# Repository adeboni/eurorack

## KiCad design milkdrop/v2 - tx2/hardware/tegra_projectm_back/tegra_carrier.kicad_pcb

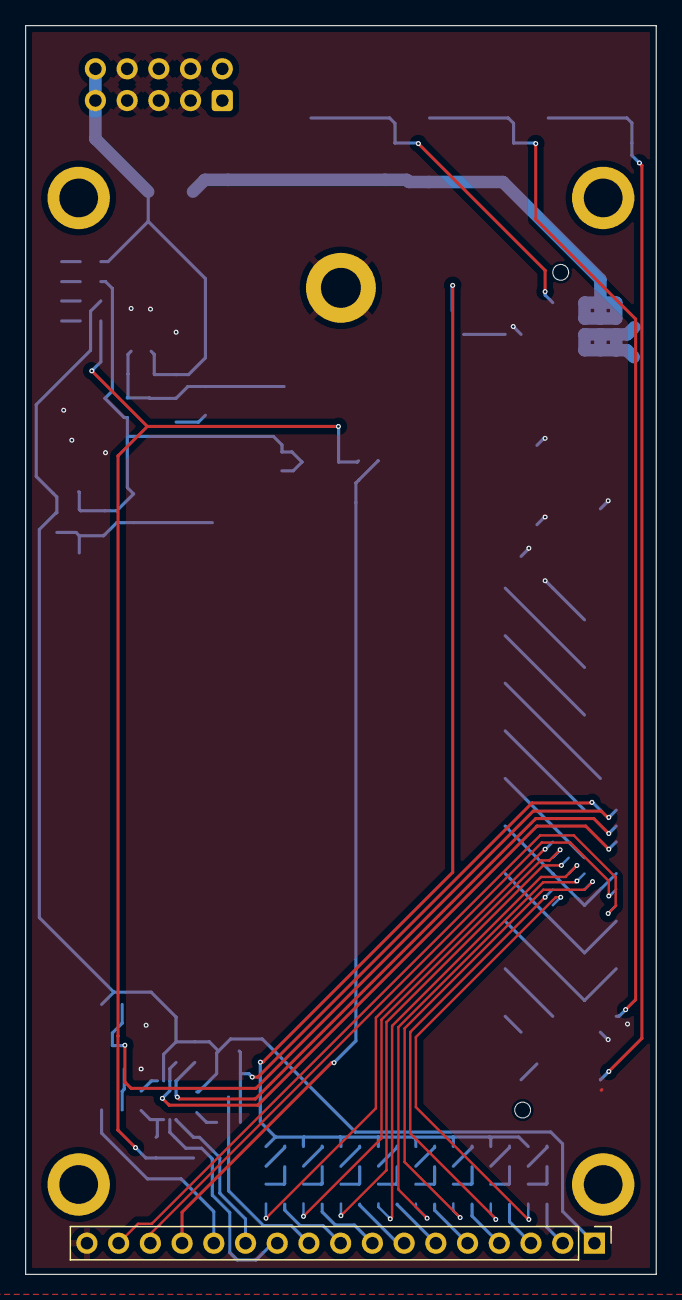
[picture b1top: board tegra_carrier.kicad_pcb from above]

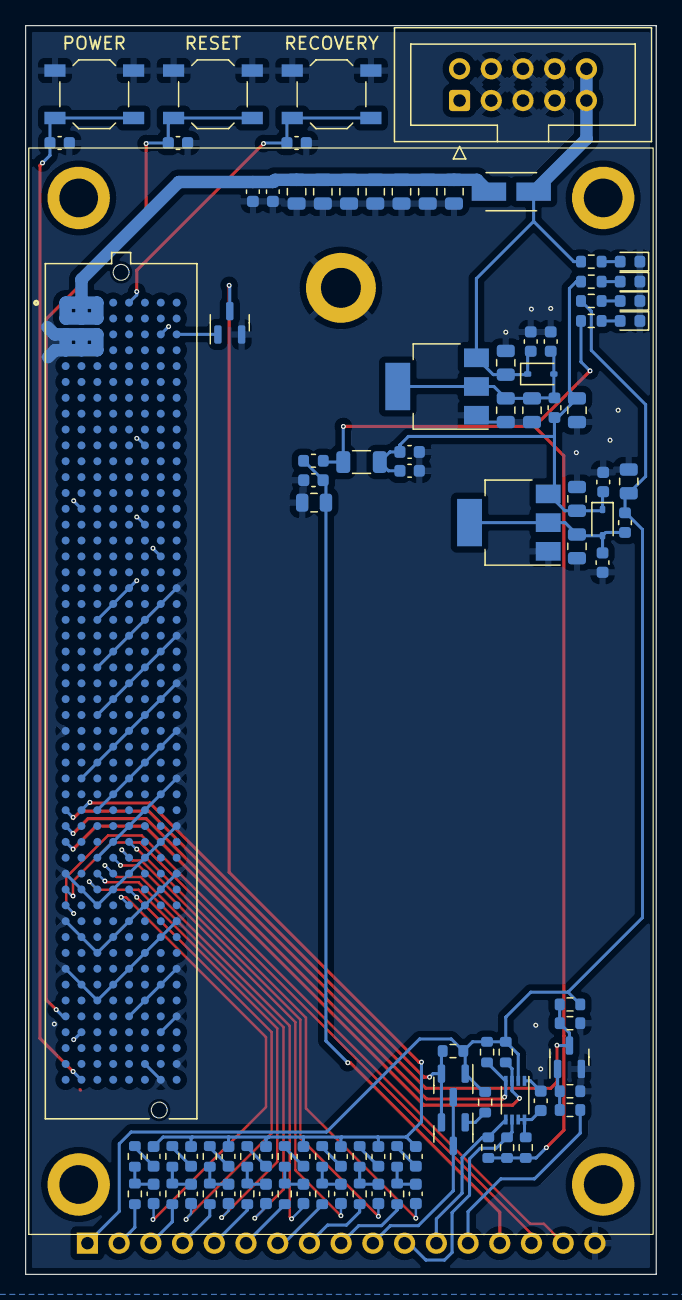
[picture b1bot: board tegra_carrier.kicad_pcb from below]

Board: 2 copper layers, 50.5 x 100.0 mm, 100 parts (99 on the bottom side), 63 nets.

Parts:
C1, C2, C3, C4, C5, C6, C7, C8, C9, C10, C17, C26, C38: 22u; C_0805_2012Metric
C11, C12, C13, C18, C20, C24, C25, C28, C29, C30, C31, C32, C33, C34, C35, C44: 100n; C_0603_1608Metric
C14, C15, C27: 10n; C_0603_1608Metric
C16, C19: 47u; C_0805_2012Metric
C22: 100p; C_0603_1608Metric
C23: 10u; C_0603_1608Metric
D1, D2: 1N5819WS; D_SOD-323
D3, D6, D26, D28: LED; LED_0603_1608Metric
D4: BAS70-05-7-F; SOT-23
FB1, FB2: MPZ1608S221; L_0603_1608Metric
H1: MountingHole_Pad; MountingHole_3.2mm_M3_DIN965_Pad
J1: SEAM-50-02.0-S-08-2-A-K-TR; SAMTEC_SEAM-50-02.0-S-08-2-A-K-TR
J3: Conn_02x05_Odd_Even; IDC-Header_2x05_P2.54mm_Vertical
J4: Conn_01x17; PinHeader_1x17_P2.54mm_Vertical
L1: BLM18AG102; L_0603_1608Metric
L2, L3, L4, L5, L6, L7, L8, L9: MI0603J601R-10; L_0603_1608Metric
L11: FERRITE_10A; FB_28F0121-0SR-10
Q1: BC846; SOT-23
Q2, Q5: BSS138; SOT-23
R1: 330; R_0603_1608Metric
R4, R6: 10k; R_0603_1608Metric
R7, R9: 100k; R_0603_1608Metric
R10: 200k; R_0603_1608Metric
R11: 162k; R_0603_1608Metric
R13, R14, R15, R16, R55: 2.2k; R_0603_1608Metric
R18: 31.6k; R_0603_1608Metric
R22, R57: 1k; R_0603_1608Metric
R23, R24, R25, R26, R27, R28, R29, R30: 4.7; R_0603_1608Metric
R31, R32, R33, R34, R35, R36, R37, R38: 499; R_0603_1608Metric
SW1, SW2, SW3: SW_Push; SW_SPST_TL3342
TH1: 1206L020C; R_1206_3216Metric
U1: AMS1117-3.3; SOT-223-3_TabPin2
U3: PCA9306DC; VSSOP-8_2.3x2mm_P0.5mm
U15: AMS1117-5.0; SOT-223-3_TabPin2

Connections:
5V_HDMI: L1.1, R10.1, R15.1, R16.1, R22.1, TH1.1
+3V3: C16.1, FB2.2, J4.1, Q2.1 (G), R1.1, R4.1, R11.2, R13.1, R14.1, R18.2, U3.2 (VREF1)
+5V: C10.2, C17.1, C18.1, C23.1, C24.1, D2.1 (K), FB1.2, R57.1, TH1.2, U1.3 (VI)
+12V: C9.2, C44.1, D1.1 (K), J3.9, J3.10, L11.1, R55.1, U15.3 (VI)
DP1_TXD0_N: C29.1, J1.E38
DP1_TXD0_P: C28.1, J1.E39
DP1_TXD1_N: C31.1, J1.C37
DP1_TXD1_P: C30.1, J1.C38
DP1_TXD2_N: C33.1, J1.D36
DP1_TXD2_P: C32.1, J1.D37
DP1_TXD3_N: C35.1, J1.E35
DP1_TXD3_P: C34.1, J1.E36
FORCE_RECOVERY_L: C27.1, J1.E1, SW3.2
GND: C1.1, C2.1, C3.1, C4.1, C5.1, C6.1, C7.1, C8.1, C9.1, C10.1, C11.2, C12.2, C13.2, C14.2, C15.2, C16.2, C17.2, C18.2, C19.2, C20.2, C22.2, C23.2, C24.2, C25.2, C26.1, C27.2, C38.1, C44.2, D3.1 (K), D6.1 (K), D26.1 (K), D28.1 (K), H1.1, J1.A3, J1.A4, J1.A28, J1.A37, J1.A40, J1.A43, J1.B3, J1.B4, J1.B14, J1.B31, J1.B38, J1.B41, J1.B44, J1.B47, J1.C3, J1.C4, J1.C21, J1.C24, J1.C27, J1.C30, J1.C33, J1.C36, J1.C39, J1.C42, J1.C45, J1.D20, J1.D23, J1.D26, J1.D29, J1.D32, J1.D35, J1.D38, J1.D41, J1.D44, J1.E19, J1.E22, J1.E25, J1.E28, J1.E31, J1.E34, J1.E37, J1.E40, J1.E43, J1.E46, J1.F10, J1.F15, J1.F21, J1.F24, J1.F27, J1.F30, J1.F33, J1.F36, J1.F39, J1.F42, J1.F45, J1.F49, J1.G3, J1.G17, J1.G20, J1.G23, J1.G26, J1.G29, J1.G32, J1.G35, J1.G38, J1.G41, J1.G44, J1.G47, J1.G50, J1.H19, J1.H22, J1.H25, J1.H28, J1.H31, J1.H34, J1.H37, J1.H40, J1.H43, J1.H46, J1.H49, J3.3, J3.4, J3.5, J3.6, J3.7, J3.8, J4.17, Q1.2 (E), Q5.2 (S), R6.2, R9.2, SW1.1, SW2.1, SW3.1, U1.1 (GND), U3.1 (GND), U15.1 (GND)
HDMI_5V_CABLE: C25.1, C26.2, J4.14, L1.2
HDMI_CEC: D4.2 (A), J1.B33, Q2.2 (S), R11.1
HDMI_CEC_CON: D4.3 (K), J4.10, Q2.3 (D)
HDMI_CKN_CON: J4.9, R30.2
HDMI_CKP_CON: J4.8, R29.2
HDMI_D0N_CON: J4.7, R28.2
HDMI_D0P_CON: J4.6, R27.2
HDMI_D1N_CON: J4.5, R26.2
HDMI_D1P_CON: J4.4, R25.2
HDMI_D2N_CON: J4.3, R24.2
HDMI_D2P_CON: J4.2, R23.2
HDMI_DDC_SCL_5V0: J4.11, R15.2, U3.6 (SCL2)
HDMI_DDC_SCL_POL: J1.A35, R13.2, U3.3 (SCL1)
HDMI_DDC_SDA_5V0: J4.12, R16.2, U3.5 (SDA2)
HDMI_DDC_SDA_POL: J1.A34, R14.2, U3.4 (SDA1)
HDMI_HPD_CON: J4.13, R7.2
HDMI_HPD_L: J1.A33, Q1.3 (C), R4.2, R6.1
unnamed: C28.2, R23.1, R31.2
unnamed: C29.2, R24.1, R32.2
unnamed: C30.2, R25.1, R33.2
unnamed: C31.2, R26.1, R34.2
unnamed: C32.2, R27.1, R35.2
unnamed: C33.2, R28.1, R36.2
unnamed: C34.2, R29.1, R37.2
unnamed: C35.2, R30.1, R38.2
unnamed: C7.2, C8.2, C13.1, D1.2 (A), FB1.1, U15.2 (VO)
unnamed: C19.1, C20.1, D2.2 (A), FB2.1, U1.2 (VO)
unnamed: D3.2 (A), R1.2
unnamed: D4.1 (A), R18.1
unnamed: D6.2 (A), R22.2
unnamed: D26.2 (A), R57.2
unnamed: D28.2 (A), R55.2
unnamed: L2.2, R31.1
unnamed: L3.2, R32.1
unnamed: L4.2, R33.1
unnamed: L5.2, R34.1
unnamed: L6.2, R35.1
unnamed: L7.2, R36.1
unnamed: L8.2, R37.1
unnamed: L9.2, R38.1
unnamed: Q1.1 (B), R7.1, R9.1
unnamed: L2.1, L3.1, L4.1, L5.1, L6.1, L7.1, L8.1, L9.1, Q5.3 (D)
unnamed: C22.1, R10.2, U3.7 (VREF2), U3.8 (EN)
P12V_TX2: C1.2, C2.2, C3.2, C4.2, C5.2, C6.2, C11.1, C12.1, C38.2, J1.A1, J1.A2, J1.B1, J1.B2, J1.C1, J1.C2, L11.2
POWER_BTN_L: C15.1, J1.B50, SW1.2
SOM_GPIO20_HDMI_TERM: J1.H3, Q5.1 (G)
SOM_RESET_OUT_L: C14.1, J1.A46, SW2.2
USB1_D_N: J1.A39, J4.16
USB1_D_P: J1.A38, J4.15

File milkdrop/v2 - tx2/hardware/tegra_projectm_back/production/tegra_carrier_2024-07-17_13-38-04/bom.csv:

Designator,Footprint,Quantity,Value,LCSC Part #
"C1, C10, C17, C2, C26, C3, C38, C4, C5, C6, C7, C8, C9",805,13,22u,C45783
"C11, C12, C13, C18, C20, C24, C25, C28, C29, C30, C31, C32, C33, C34, C35, C44",603,16,100n,C14663
"C14, C15, C27",603,3,10n,C57112
"C16, C19",805,2,47u,C16780
C22,603,1,100p,C14858
C23,603,1,10u,C96446
"D1, D2",D_SOD-323,2,1N5819WS,C191023
"D26, D28, D3, D6",603,4,LED,C2286
D4,SOT-23,1,BAS70-05-7-F,C134376
J1,SAMTEC_SEAM-50-02.0-S-08-2-A-K-TR,1,SEAM-50-02.0-S-08-2-A-K-TR,C6473445
L11,FB_28F0121-0SR-10,1,FERRITE_10A,C6341404
"FB1, FB2, L1, L2, L3, L4, L5, L6, L7, L8, L9",603,11,MI0603J601R-10,C1002
Q1,SOT-23,1,BC846,C20069134
"Q2, Q5",SOT-23,2,BSS138,C7420339
R1,603,1,330,C23138
R10,603,1,200k,C25811
R11,603,1,162k,C22813
"R13, R14, R15, R16, R55",603,5,2.2k,C4190
R18,603,1,31.6k,C4216
"R22, R57",603,2,1k,C21190
"R23, R24, R25, R26, R27, R28, R29, R30",603,8,4.7,C23164
"R31, R32, R33, R34, R35, R36, R37, R38",603,8,499,C23065
"R4, R6",603,2,10k,C25804
"R7, R9",603,2,100k,C25803
"SW1, SW2, SW3",SW_SPST_TL3342,3,SW_Push,C318884
TH1,1206,1,1206L020C,C207035
U1,SOT-223-3_TabPin2,1,AMS1117-3.3,C6186
U15,SOT-223-3_TabPin2,1,AMS1117-5.0,C6187
U3,VSSOP-8_2.3x2mm_P0.5mm,1,PCA9306DC,C33196

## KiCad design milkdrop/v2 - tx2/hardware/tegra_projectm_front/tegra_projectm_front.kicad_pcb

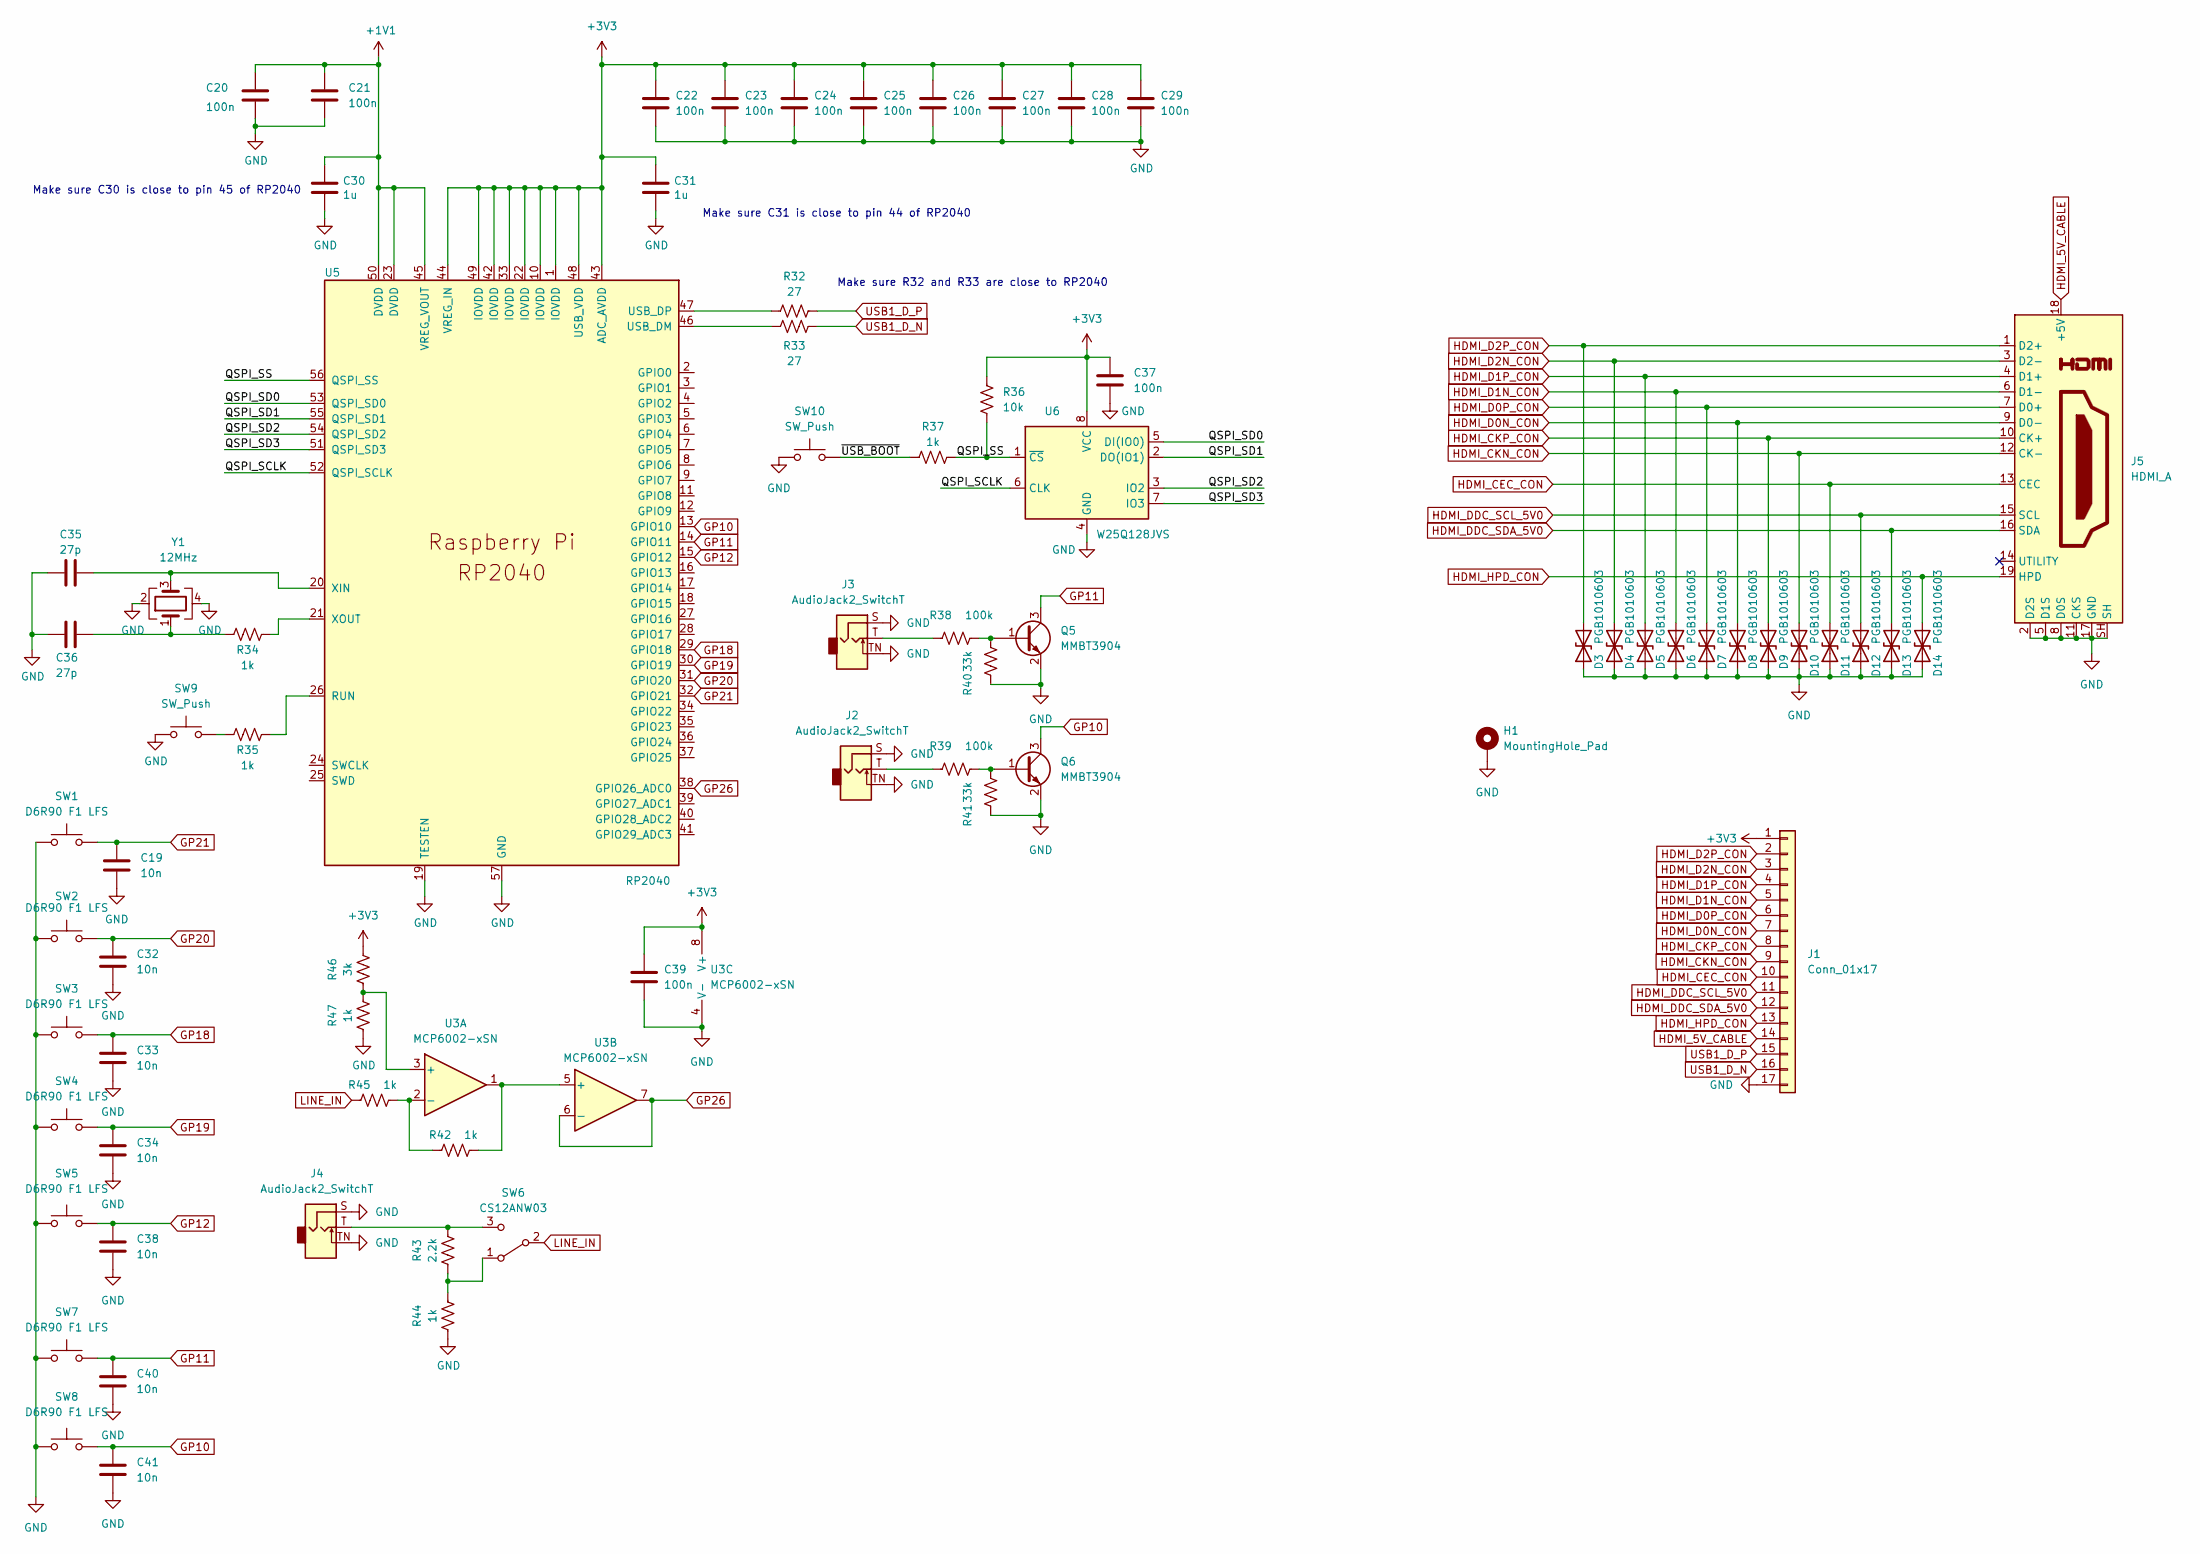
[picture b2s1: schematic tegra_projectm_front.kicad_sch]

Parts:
C19, C32, C33, C34, C38, C40, C41: 10n; C_0603_1608Metric
C20, C21, C22, C23, C24, C25, C26, C27, C28, C29, C37, C39: 100n; C_0603_1608Metric
C30, C31: 1u; C_0603_1608Metric
C35, C36: 27p; C_0603_1608Metric
D3, D4, D5, D6, D7, D8, D9, D10, D11, D12, D13, D14: PGB1010603; D_0603_1608Metric
H1: MountingHole_Pad; MountingHole_3.2mm_M3_DIN965_Pad
J1: Conn_01x17; PinSocket_1x17_P2.54mm_Vertical
J2, J3, J4: AudioJack2_SwitchT; Jack_3.5mm_QingPu_WQP-PJ398SM_Vertical_CircularHoles
J5: HDMI_A; MOLEX_476591101
Q5, Q6: MMBT3904; SOT-23
R32, R33: 27; R_0603_1608Metric
R34, R35, R37, R42, R44, R45, R47: 1k; R_0603_1608Metric
R36: 10k; R_0603_1608Metric
R38, R39: 100k; R_0603_1608Metric
R40, R41: 33k; R_0603_1608Metric
R43: 2.2k; R_0603_1608Metric
R46: 3k; R_0603_1608Metric
SW1, SW2, SW3, SW4, SW5, SW7, SW8: D6R90 F1 LFS; Push_E-Switch_KS01Q01
SW6: CS12ANW03
SW9, SW10: SW_Push; SW_SPST_TL3342
U3: MCP6002-xSN; SOIC-8_3.9x4.9mm_P1.27mm
U5: RP2040; QFN-56-1EP_7x7mm_P0.4mm_EP3.2x3.2mm
U6: W25Q128JVS; SOIC-8_5.23x5.23mm_P1.27mm
Y1: 12MHz; Crystal_SMD_3225-4Pin_3.2x2.5mm

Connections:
+1V1: C20.1, C21.1, C30.1, U5.23 (DVDD), U5.45 (VREG_VOUT), U5.50 (DVDD)
+3V3: C22.1, C23.1, C24.1, C25.1, C26.1, C27.1, C28.1, C29.1, C31.1, C37.1, C39.1, J1.1, R36.2, R46.1, U3.8 (V+), U5.1 (IOVDD), U5.10 (IOVDD), U5.22 (IOVDD), U5.33 (IOVDD), U5.42 (IOVDD), U5.43 (ADC_AVDD), U5.44 (VREG_IN), U5.48 (USB_VDD), U5.49 (IOVDD), U6.8 (VCC)
/QSPI_SCLK: U5.52 (QSPI_SCLK), U6.6 (CLK)
/QSPI_SD0: U5.53 (QSPI_SD0), U6.5 (DI(IO0))
/QSPI_SD1: U5.55 (QSPI_SD1), U6.2 (DO(IO1))
/QSPI_SD2: U5.54 (QSPI_SD2), U6.3 (IO2)
/QSPI_SD3: U5.51 (QSPI_SD3), U6.7 (IO3)
/QSPI_SS: R36.1, R37.2, U5.56 (QSPI_SS), U6.1 (~CS)
/~USB_BOOT: R37.1, SW10.2
GND: C19.2, C20.2, C21.2, C22.2, C23.2, C24.2, C25.2, C26.2, C27.2, C28.2, C29.2, C30.2, C31.2, C32.2, C33.2, C34.2, C35.2, C36.2, C37.2, C38.2, C39.2, C40.2, C41.2, D3.1 (A1), D4.1 (A1), D5.1 (A1), D6.1 (A1), D7.1 (A1), D8.1 (A1), D9.1 (A1), D10.1 (A1), D11.1 (A1), D12.1 (A1), D13.1 (A1), D14.1 (A1), H1.1, J1.17, J2.S, J2.TN, J3.S, J3.TN, J4.S, J4.TN, J5.2 (D2S), J5.5 (D1S), J5.8 (D0S), J5.11 (CKS), J5.17 (GND), J5.SH, Q5.2 (E), Q6.2 (E), R40.1, R41.1, R44.2, R47.2, SW1.1, SW2.1, SW3.1, SW4.1, SW5.1, SW7.1, SW8.1, SW9.1, SW10.1, U3.4 (V-), U5.19 (TESTEN), U5.57 (GND), U6.4 (GND), Y1.2, Y1.4
GP10: C41.1, Q6.3 (C), SW8.2, U5.13 (GPIO10)
GP11: C40.1, Q5.3 (C), SW7.2, U5.14 (GPIO11)
GP12: C38.1, SW5.2, U5.15 (GPIO12)
GP18: C33.1, SW3.2, U5.29 (GPIO18)
GP19: C34.1, SW4.2, U5.30 (GPIO19)
GP20: C32.1, SW2.2, U5.31 (GPIO20)
GP21: C19.1, SW1.2, U5.32 (GPIO21)
GP26: U3.6 (-), U3.7, U5.38 (GPIO26_ADC0)
HDMI_5V_CABLE: J1.14, J5.18 (+5V)
HDMI_CEC_CON: D11.2 (A2), J1.10, J5.13 (CEC)
HDMI_CKN_CON: D10.2 (A2), J1.9, J5.12 (CK-)
HDMI_CKP_CON: D9.2 (A2), J1.8, J5.10 (CK+)
HDMI_D0N_CON: D8.2 (A2), J1.7, J5.9 (D0-)
HDMI_D0P_CON: D7.2 (A2), J1.6, J5.7 (D0+)
HDMI_D1N_CON: D6.2 (A2), J1.5, J5.6 (D1-)
HDMI_D1P_CON: D5.2 (A2), J1.4, J5.4 (D1+)
HDMI_D2N_CON: D4.2 (A2), J1.3, J5.3 (D2-)
HDMI_D2P_CON: D3.2 (A2), J1.2, J5.1 (D2+)
HDMI_DDC_SCL_5V0: D12.2 (A2), J1.11, J5.15 (SCL)
HDMI_DDC_SDA_5V0: D13.2 (A2), J1.12, J5.16 (SDA)
HDMI_HPD_CON: D14.2 (A2), J1.13, J5.19 (HPD)
LINE_IN: R45.1, SW6.2 (B)
unnamed: C36.1, R34.2, Y1.1
unnamed: J2.T, R39.1
unnamed: J3.T, R38.1
unnamed: Q5.1 (B), R38.2, R40.2
unnamed: Q6.1 (B), R39.2, R41.2
unnamed: R35.2, SW9.2
unnamed: R43.2, R44.1, SW6.1 (A)
unnamed: J4.T, R43.1, SW6.3 (C)
unnamed: R46.2, R47.1, U3.3 (+)
unnamed: R42.1, R45.2, U3.2 (-)
unnamed: R42.2, U3.1, U3.5 (+)
unnamed: R35.1, U5.26 (RUN)
unnamed: R33.1, U5.46 (USB_DM)
unnamed: R32.1, U5.47 (USB_DP)
unnamed: C35.1, U5.20 (XIN), Y1.3
unnamed: R34.1, U5.21 (XOUT)
USB1_D_N: J1.16, R33.2
USB1_D_P: J1.15, R32.2

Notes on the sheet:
Make sure R32 and R33 are close to RP2040
Make sure C30 is close to pin 45 of RP2040
Make sure C31 is close to pin 44 of RP2040

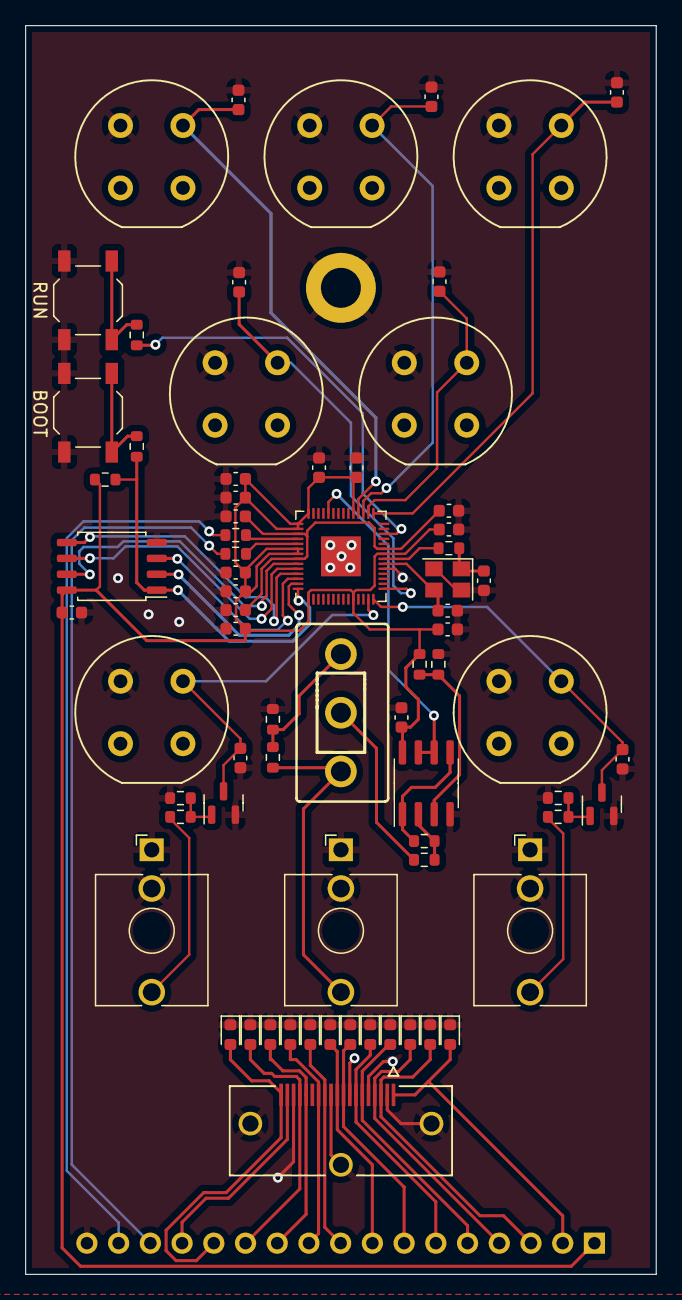
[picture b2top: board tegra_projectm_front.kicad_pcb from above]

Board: 2 copper layers, 50.5 x 100.0 mm, 73 parts (1 on the bottom side), 50 nets.

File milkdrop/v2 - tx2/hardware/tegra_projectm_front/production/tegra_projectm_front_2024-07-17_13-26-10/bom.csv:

Designator,Footprint,Quantity,Value,LCSC Part #
"C19, C32, C33, C34, C38, C40, C41",603,7,10n,C57112
"C20, C21, C22, C23, C24, C25, C26, C27, C28, C29, C37, C39",603,12,100n,C14663
"C30, C31",603,2,1u,C15849
"C35, C36",603,2,27p,C1647
"D10, D11, D12, D13, D14, D3, D4, D5, D6, D7, D8, D9",603,12,PGB1010603,C10677
J5,MOLEX_476591101,1,HDMI_A,C2682172
"Q5, Q6",SOT-23,2,MMBT3904,C20526
"R32, R33",603,2,27,C25190
"R34, R35, R37, R42, R44, R45, R47",603,7,1k,C21190
R36,603,1,10k,C25804
"R38, R39",603,2,100k,C25803
"R40, R41",603,2,33k,C4216
R43,603,1,2.2k,C4190
R46,603,1,3k,C4211
"SW10, SW9",SW_SPST_TL3342,2,SW_Push,C318884
U3,SOIC-8_3.9x4.9mm_P1.27mm,1,MCP6002-xSN,C7377
U5,QFN-56-1EP_7x7mm_P0.4mm_EP3.2x3.2mm,1,RP2040,C2040
U6,SOIC-8_5.23x5.23mm_P1.27mm,1,W25Q128JVS,C97521
Y1,Crystal_SMD_3225-4Pin_3.2x2.5mm,1,12MHz,C9002

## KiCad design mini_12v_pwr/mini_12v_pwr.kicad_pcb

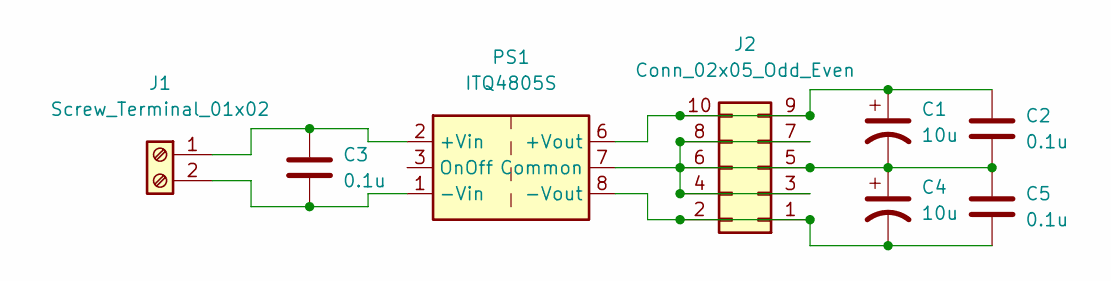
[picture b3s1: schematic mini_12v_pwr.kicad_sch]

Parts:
C1, C4: 10u; CP_Radial_D5.0mm_P2.50mm
C2, C3, C5: 0.1u; C_Disc_D3.4mm_W2.1mm_P2.50mm
J1: Screw_Terminal_01x02; TerminalBlock_Phoenix_PT-1,5-2-3.5-H_1x02_P3.50mm_Horizontal
J2: Conn_02x05_Odd_Even; PinSocket_2x05_P2.54mm_Vertical
PS1: ITQ4805S; Converter_DCDC_XP_POWER-ITxxxxxS_THT

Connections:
unnamed: C1.1, C2.1, J2.9, J2.10, PS1.6 (+Vout)
unnamed: C1.2, C2.2, C4.1, C5.1, J2.3, J2.4, J2.5, J2.6, J2.7, J2.8, PS1.7 (Common)
unnamed: C3.1, J1.1, PS1.2 (+Vin)
unnamed: C3.2, J1.2, PS1.1 (-Vin)
unnamed: C4.2, C5.2, J2.1, J2.2, PS1.8 (-Vout)

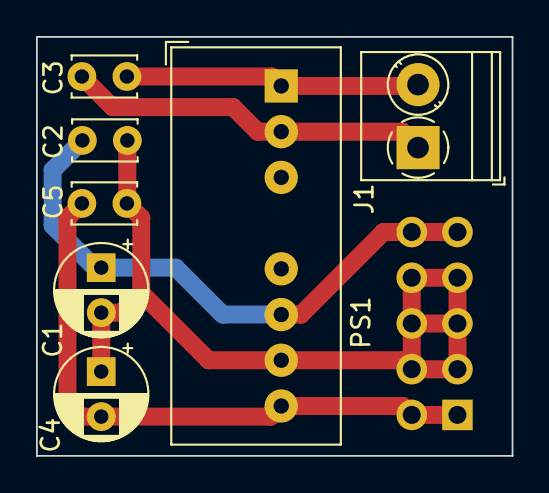
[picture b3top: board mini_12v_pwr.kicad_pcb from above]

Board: 2 copper layers, 26.4 x 23.3 mm, 8 parts (1 on the bottom side), 5 nets.

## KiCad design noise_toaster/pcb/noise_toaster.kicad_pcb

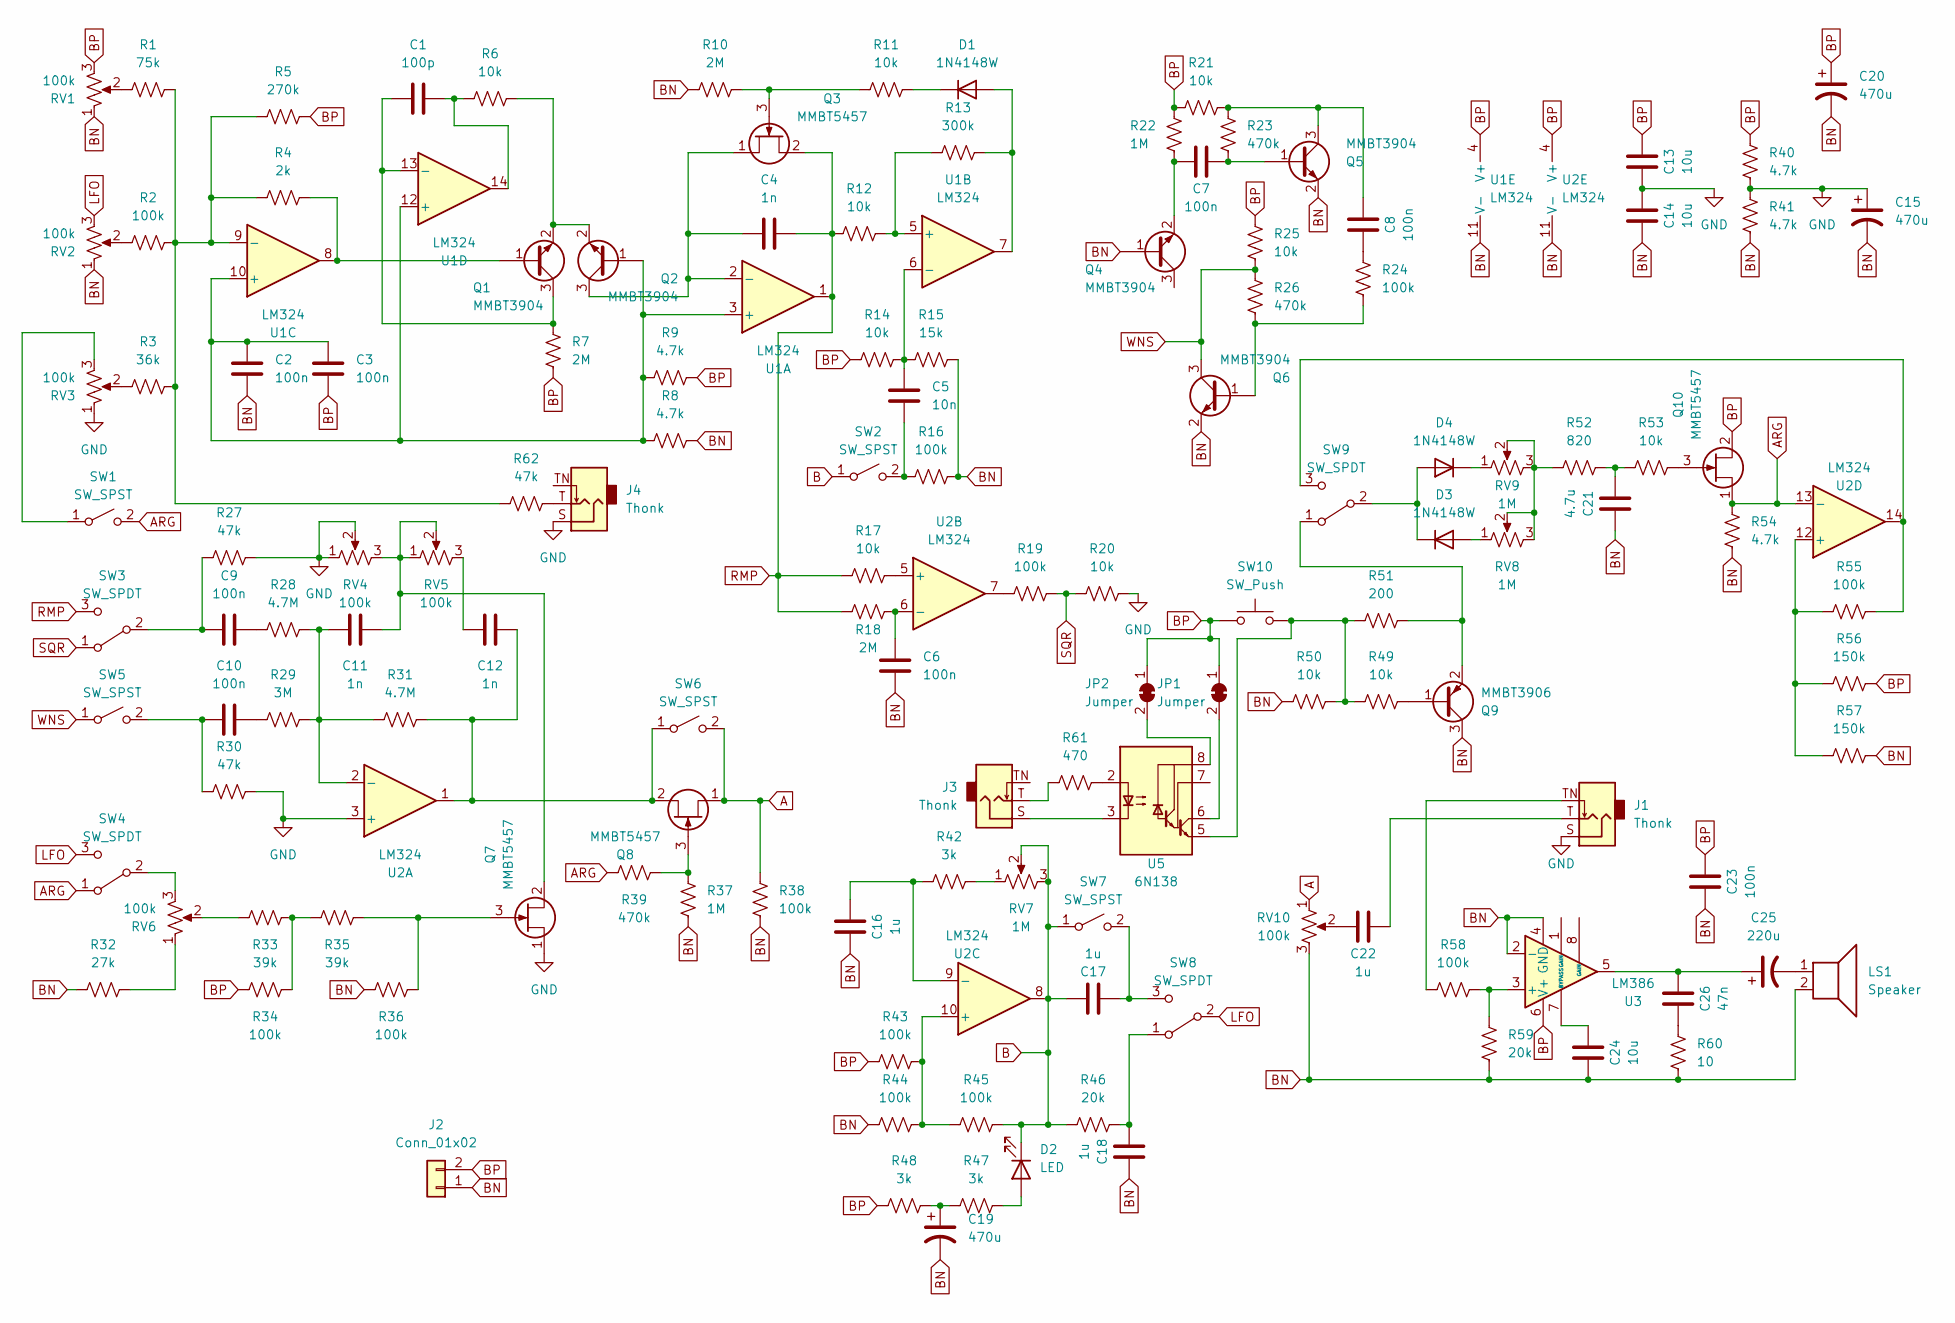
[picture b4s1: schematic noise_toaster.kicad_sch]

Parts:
C1: 100p; C_0603_1608Metric
C2, C3, C6, C7, C8, C9, C10, C23: 100n; C_0603_1608Metric
C4, C11, C12: 1n; C_0603_1608Metric
C5: 10n; C_0603_1608Metric
C13, C14, C24: 10u; C_0603_1608Metric
C15, C19, C20: 470u; CP_Radial_D8.0mm_P3.50mm
C16, C17, C18, C22: 1u; C_0603_1608Metric
C21: 4.7u; C_0603_1608Metric
C25: 220u; CP_Radial_D8.0mm_P3.50mm
C26: 47n; C_0603_1608Metric
D1, D3, D4: 1N4148W; D_SOD-123
D2: LED; LED_D5.0mm
J1, J3, J4: Thonk; Jack_3.5mm_QingPu_WQP-PJ301M-12_Vertical
J2: Conn_01x02; PinHeader_1x02_P2.54mm_Vertical
JP1, JP2: Jumper; SolderJumper-2_P1.3mm_Bridged_RoundedPad1.0x1.5mm
LS1: Speaker; PinHeader_1x02_P2.54mm_Vertical
Q1, Q2, Q4, Q5, Q6: MMBT3904; SOT-23
Q3, Q7, Q8, Q10: MMBT5457; SOT-23
Q9: MMBT3906; SOT-23
R1: 75k; R_0603_1608Metric
R2, R16, R19, R24, R34, R36, R38, R43, R44, R45, R55, R58: 100k; R_0603_1608Metric
R3: 36k; R_0603_1608Metric
R4: 2k; R_0603_1608Metric
R5: 270k; R_0603_1608Metric
R6, R11, R12, R14, R17, R20, R21, R25, R49, R50, R53: 10k; R_0603_1608Metric
R7, R10, R18: 2M; R_0603_1608Metric
R8, R9, R40, R41, R54: 4.7k; R_0603_1608Metric
R13: 300k; R_0603_1608Metric
R15: 15k; R_0603_1608Metric
R22, R37: 1M; R_0603_1608Metric
R23, R26, R39: 470k; R_0603_1608Metric
R27, R30, R62: 47k; R_0603_1608Metric
R28, R31: 4.7M; R_0603_1608Metric
R29: 3M; R_0603_1608Metric
R32: 27k; R_0603_1608Metric
R33, R35: 39k; R_0603_1608Metric
R42, R47, R48: 3k; R_0603_1608Metric
R46, R59: 20k; R_0603_1608Metric
R51: 200; R_0603_1608Metric
R52: 820; R_0603_1608Metric
R56, R57: 150k; R_0603_1608Metric
R60: 10; R_0603_1608Metric
R61: 470; R_0603_1608Metric
RV1, RV2, RV3, RV4, RV5, RV6: 100k; Potentiometer_Alpha_RD901F-40-00D_Single_Vertical
RV7, RV8, RV9: 1M; Potentiometer_Alpha_RD901F-40-00D_Single_Vertical
RV10: 100k; PinHeader_1x03_P2.54mm_Vertical
SW1, SW2, SW5, SW6, SW7: SW_SPST; Switch_Toggle_SPDT_Mini_SolderLug
SW3, SW4, SW8, SW9: SW_SPDT; Switch_Toggle_SPDT_Mini_SolderLug
SW10: SW_Push; Push_E-Switch_KS01Q01
U1, U2: LM324; SOIC-14_3.9x8.7mm_P1.27mm
U3: LM386; SOIC-8_3.9x4.9mm_P1.27mm
U5: 6N138; DIP-8_W7.62mm

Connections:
A: Q8.1 (S), R38.2, RV10.1, SW6.2 (B)
ARG: Q10.1 (S), R39.1, R54.2, SW1.2 (B), SW4.1 (A), U2.13 (-)
B: C17.2, D2.1 (K), R45.2, R46.1, RV7.2, RV7.3, SW2.1 (A), SW7.1 (A), U2.8
BN: C2.1, C6.1, C14.1, C15.2, C16.1, C18.2, C19.2, C20.2, C21.2, C23.1, C24.1, J2.1, LS1.2, Q4.1 (B), Q5.2 (E), Q6.2 (E), Q9.3 (C), R8.1, R10.2, R15.1, R16.1, R32.1, R36.1, R37.1, R38.1, R41.2, R44.1, R50.1, R54.1, R57.2, R59.1, R60.1, RV1.1, RV2.1, RV10.3, U1.11 (V-), U2.11 (V-), U3.2 (-), U3.4 (GND)
BP: C3.1, C13.2, C20.1, C23.2, J2.2, JP1.1 (A), JP2.1 (A), Q10.2 (D), R5.2, R7.1, R9.1, R14.2, R21.2, R22.1, R25.1, R34.1, R40.1, R43.1, R48.1, R56.2, RV1.3, SW10.1, U1.4 (V+), U2.4 (V+), U3.6 (V+)
GND: C13.1, C14.2, C15.1, J1.S, J4.S, Q7.1 (S), R20.1, R27.2, R30.2, R40.2, R41.1, RV3.1, RV4.1, RV4.2, U2.3 (+)
LFO: RV2.3, SW4.3 (C), SW8.2 (B)
unnamed: C1.2, R6.1, U1.14
unnamed: C8.1, R24.1
unnamed: C9.1, R28.1
unnamed: C10.1, R29.1
unnamed: C12.2, RV5.3
unnamed: C19.1, R47.1, R48.2
unnamed: C21.1, R52.2, R53.1
unnamed: C22.1, RV10.2
unnamed: C22.2, J1.T
unnamed: C25.1, C26.2, U3.5
unnamed: C25.2, LS1.1
unnamed: C26.1, R60.2
unnamed: D1.2 (A), R13.1, U1.7
unnamed: D1.1 (K), R11.1
unnamed: D2.2 (A), R47.2
unnamed: D3.2 (A), RV8.1
unnamed: D3.1 (K), D4.2 (A), SW9.2 (B)
unnamed: D4.1 (K), RV9.1
unnamed: J1.TN, R58.1
unnamed: J3.T, R61.1
unnamed: J4.T, R62.2
unnamed: JP1.2 (B), U5.6 (VO2)
unnamed: JP2.2 (B), U5.8 (VCC)
unnamed: Q1.1 (B), R4.2, U1.8
unnamed: C1.1, Q1.3 (C), R7.2, U1.13 (-)
unnamed: Q1.2 (E), Q2.2 (E), R6.2
unnamed: C2.2, C3.2, Q2.1 (B), R8.2, R9.2, U1.3 (+), U1.10 (+), U1.12 (+)
unnamed: C4.1, Q2.3 (C), Q3.1 (S), U1.2 (-)
unnamed: Q3.3 (G), R10.1, R11.2
unnamed: C7.1, Q4.2 (E), R22.2
unnamed: C7.2, Q5.1 (B), R23.2
unnamed: C8.2, Q5.3 (C), R21.1, R23.1
unnamed: Q6.1 (B), R24.2, R26.2
unnamed: C11.1, Q7.2 (D), RV4.3, RV5.1, RV5.2
unnamed: Q7.3 (G), R35.2, R36.2
unnamed: C12.1, Q8.2 (D), R31.2, SW6.1 (A), U2.1
unnamed: Q8.3 (G), R37.2, R39.2
unnamed: Q9.1 (B), R49.2
unnamed: Q9.2 (E), R51.2, SW9.1 (A)
unnamed: Q10.3 (G), R53.2
unnamed: R1.1, RV1.2
unnamed: R2.1, RV2.2
unnamed: R3.1, RV3.2
unnamed: R19.2, U2.7
unnamed: R32.2, RV6.1
unnamed: R33.1, RV6.2
unnamed: R33.2, R34.2, R35.1
unnamed: R42.2, RV7.1
unnamed: R52.1, RV8.2, RV8.3, RV9.2, RV9.3
unnamed: RV3.3, SW1.1 (A)
unnamed: C5.1, R16.2, SW2.2 (B)
unnamed: C9.2, R27.1, SW3.2 (B)
unnamed: RV6.3, SW4.2 (B)
unnamed: C10.2, R30.1, SW5.2 (B)
unnamed: C17.1, SW7.2 (B), SW8.3 (C)
unnamed: C18.1, R46.2, SW8.1 (A)
unnamed: R55.2, SW9.3 (C), U2.14
unnamed: R12.1, R13.2, U1.5 (+)
unnamed: C5.2, R14.1, R15.2, U1.6 (-)
unnamed: R1.2, R2.2, R3.2, R4.1, R5.1, R62.1, U1.9 (-)
unnamed: C11.2, R28.2, R29.2, R31.1, U2.2 (-)
unnamed: R17.1, U2.5 (+)
unnamed: C6.2, R18.1, U2.6 (-)
unnamed: R43.2, R44.2, R45.1, U2.10 (+)
unnamed: C16.2, R42.1, U2.9 (-)
unnamed: R55.1, R56.1, R57.1, U2.12 (+)
unnamed: R58.2, R59.2, U3.3 (+)
unnamed: C24.2, U3.7 (BYPASS)
unnamed: R61.2, U5.2 (C1)
unnamed: J3.S, U5.3 (C2)
unnamed: R49.1, R50.2, R51.1, SW10.2, U5.5 (GND)
RMP: C4.2, Q3.2 (D), R12.2, R17.2, R18.2, SW3.3 (C), U1.1
SQR: R19.1, R20.2, SW3.1 (A)
WNS: Q6.3 (C), R25.2, R26.1, SW5.1 (A)

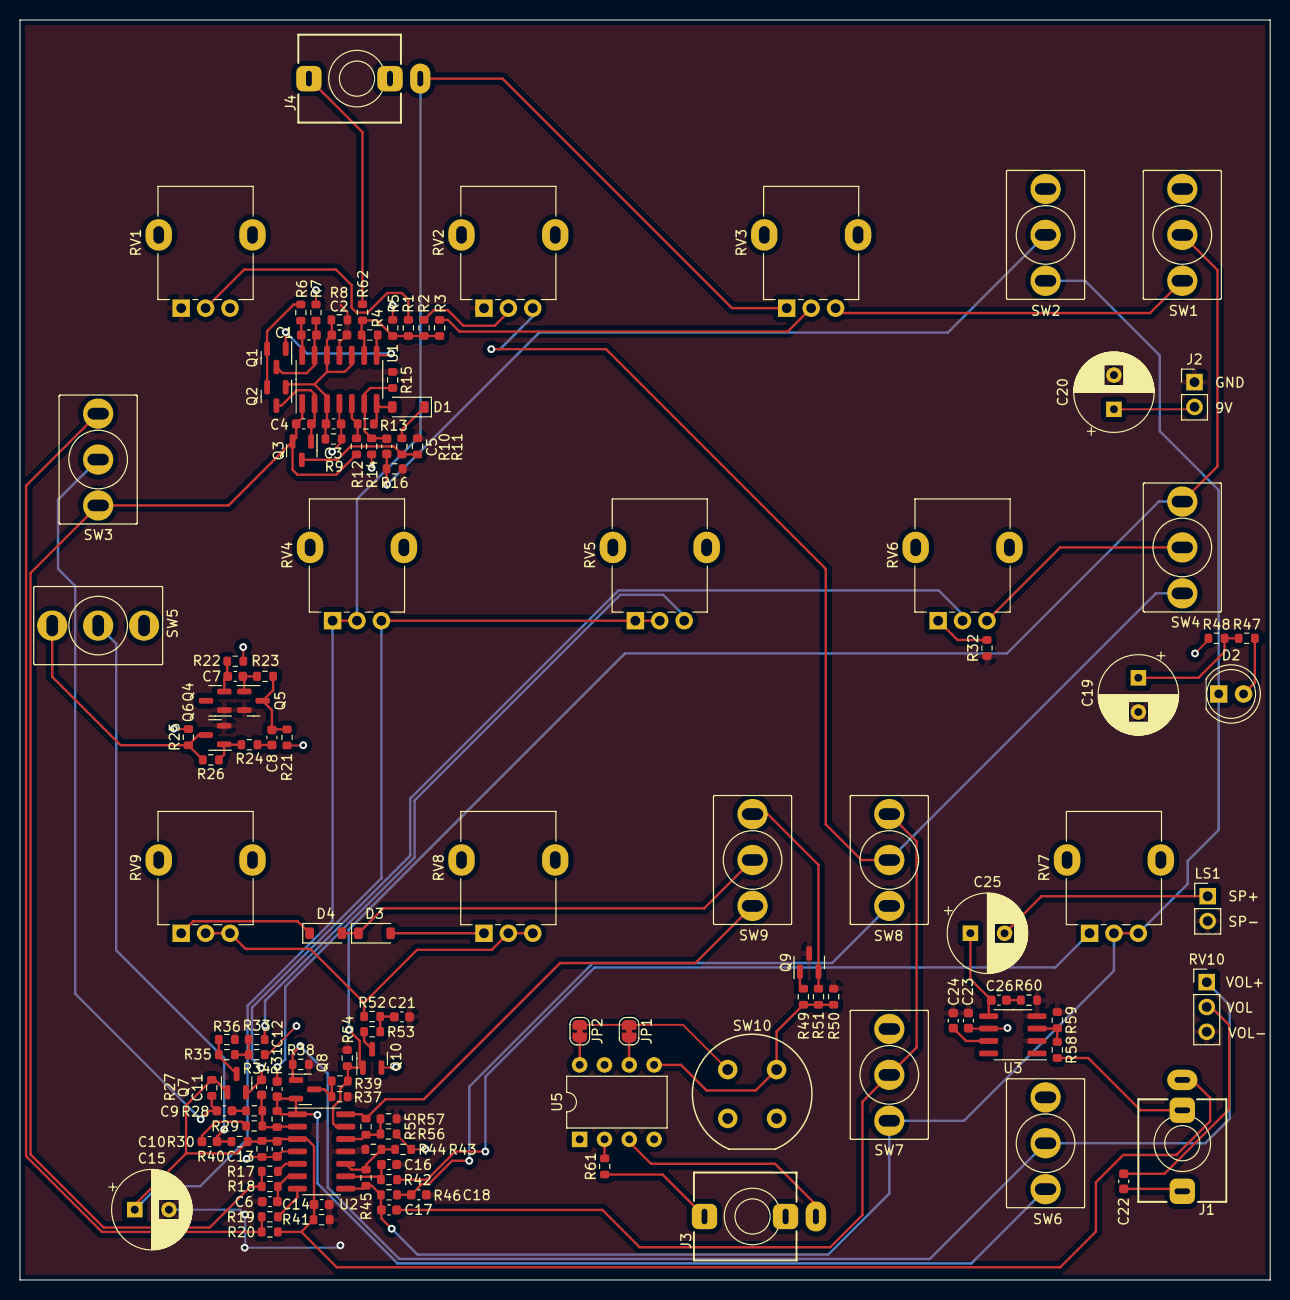
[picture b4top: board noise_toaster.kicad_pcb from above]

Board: 2 copper layers, 128.0 x 129.0 mm, 133 parts (0 on the bottom side), 81 nets.

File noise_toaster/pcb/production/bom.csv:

Designator,Footprint,Quantity,Value,LCSC Part #
C1,603,1,100p,C14858
"C10, C2, C23, C3, C6, C7, C8, C9",603,8,100n,C14663
"C11, C12, C4",603,3,1n,C1588
"C13, C14, C24",603,3,10u,C96446
"C16, C17, C18, C22",603,4,1u,C15849
C21,603,1,4.7u,C19666
C26,603,1,47n,C1622
C5,603,1,10n,C57112
"D1, D3, D4",D_SOD-123,3,1N4148W,C81598
"Q1, Q2, Q4, Q5, Q6",SOT-23,5,MMBT3904,C20526
Q9,SOT-23,1,MMBT3906,C107421
R1,603,1,75k,C23242
"R10, R18, R7",603,3,2M,C22976
"R11, R12, R14, R17, R20, R21, R25, R49, R50, R53, R6",603,11,10k,C25804
R13,603,1,300k,C23024
R15,603,1,15k,C22809
"R16, R19, R2, R24, R34, R36, R38, R43, R44, R45, R55, R58",603,12,100k,C25803
"R22, R37",603,2,1M,C22935
"R23, R26, R39",603,3,470k,C23178
"R27, R30, R62",603,3,47k,C25819
"R28, R31",603,2,4.7M,
R29,603,1,3M,
R3,603,1,36k,
R32,603,1,27k,C22967
"R33, R35",603,2,39k,C23153
R4,603,1,2k,C22975
"R40, R41, R54, R8, R9",603,5,4.7k,C23162
"R42, R47, R48",603,3,3k,C4211
"R46, R59",603,2,20k,C4184
R5,603,1,270k,
R51,603,1,200,C8218
R52,603,1,820,C23253
"R56, R57",603,2,150k,C22807
R60,603,1,10,C22859
R61,603,1,470,C23179
"U1, U2",SOIC-14_3.9x8.7mm_P1.27mm,2,LM324,C71035
U3,SOIC-8_3.9x4.9mm_P1.27mm,1,LM386,C23573
